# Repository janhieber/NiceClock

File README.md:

# About
This project was started for testing the new KiCad v4
as a replacement for EAGLE.

I want a free ECAD software without the limiations, so
I started this to explore the capabilities of KiCad.

Conclusion: KiCad can be a good replacement for EAGLE and co.  
It has some rough edges, but makes a point with some
great features.

# Nice 3D pics :)

# Current progress
### Hardware

TODO:  
- [ ] schematic
  - [x] LEDs and WS2803 ICs
    - [x] wire up
    - [x] connect to CPU
  - [x] CPU (STM32F1)
  - [ ] real time clock
    - [x] wire up
    - [x] connect to CPU
  - [x] SWD program and serial terminal
- [ ] layout
  - [ ] LEDs
  - [ ] WS2803
  - [ ] STM32 CPU
  - [x] RTC
  - [x] power supply

For the current progress, look at the
[schematic](https://raw.githubusercontent.com/janhieber/NiceClock/master/hardware/doc/schematic.pdf)
and
[layout](https://raw.githubusercontent.com/janhieber/NiceClock/master/hardware/doc/board.pdf) PDFs.

### Software
Software development not started yes.

The software will be written in pure C.  
STM32CubeMX will be used as initialisation code generator.

TODO:  
- [ ] STM32 software
  - [ ] hardware initialisation
  - [ ] cooperative scheduler
  - [ ] real time clock code
  - [ ] LED control code for WS2803 ICs via SPI
  - [ ] DCF77 code
  - [ ] Bootloader for serial program download over UART
- [ ] Software to flash firmware via serial connection

# Community
If you are interessted in this, feel free to contact me.  
I'll also have some spare PCBs when I ordner them, so I'll sell them.

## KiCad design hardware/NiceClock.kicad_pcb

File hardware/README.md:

### Schematic and layout
The schematic and layout was/is created with KiCad version 4.

I'm using some custom symbols, mods and 3D models, they are all
in this folder.

### LED placement
First I placed the LEDs manually. I have drawn a few
circles on the layout and lines from the middle in ~6° steps...

All in all that was really messy and not the way I used to work.  
So I wrote a small Python program to calculate position and angle
of every LED and wite it to the layout file.

Check out the scrit in the *scripts* folder.

### BOM
BOM generation is done using the *bom2csv.xsl* plugin.
Most schemativ parts have a *R* attribute with the reichelt.de
part number.

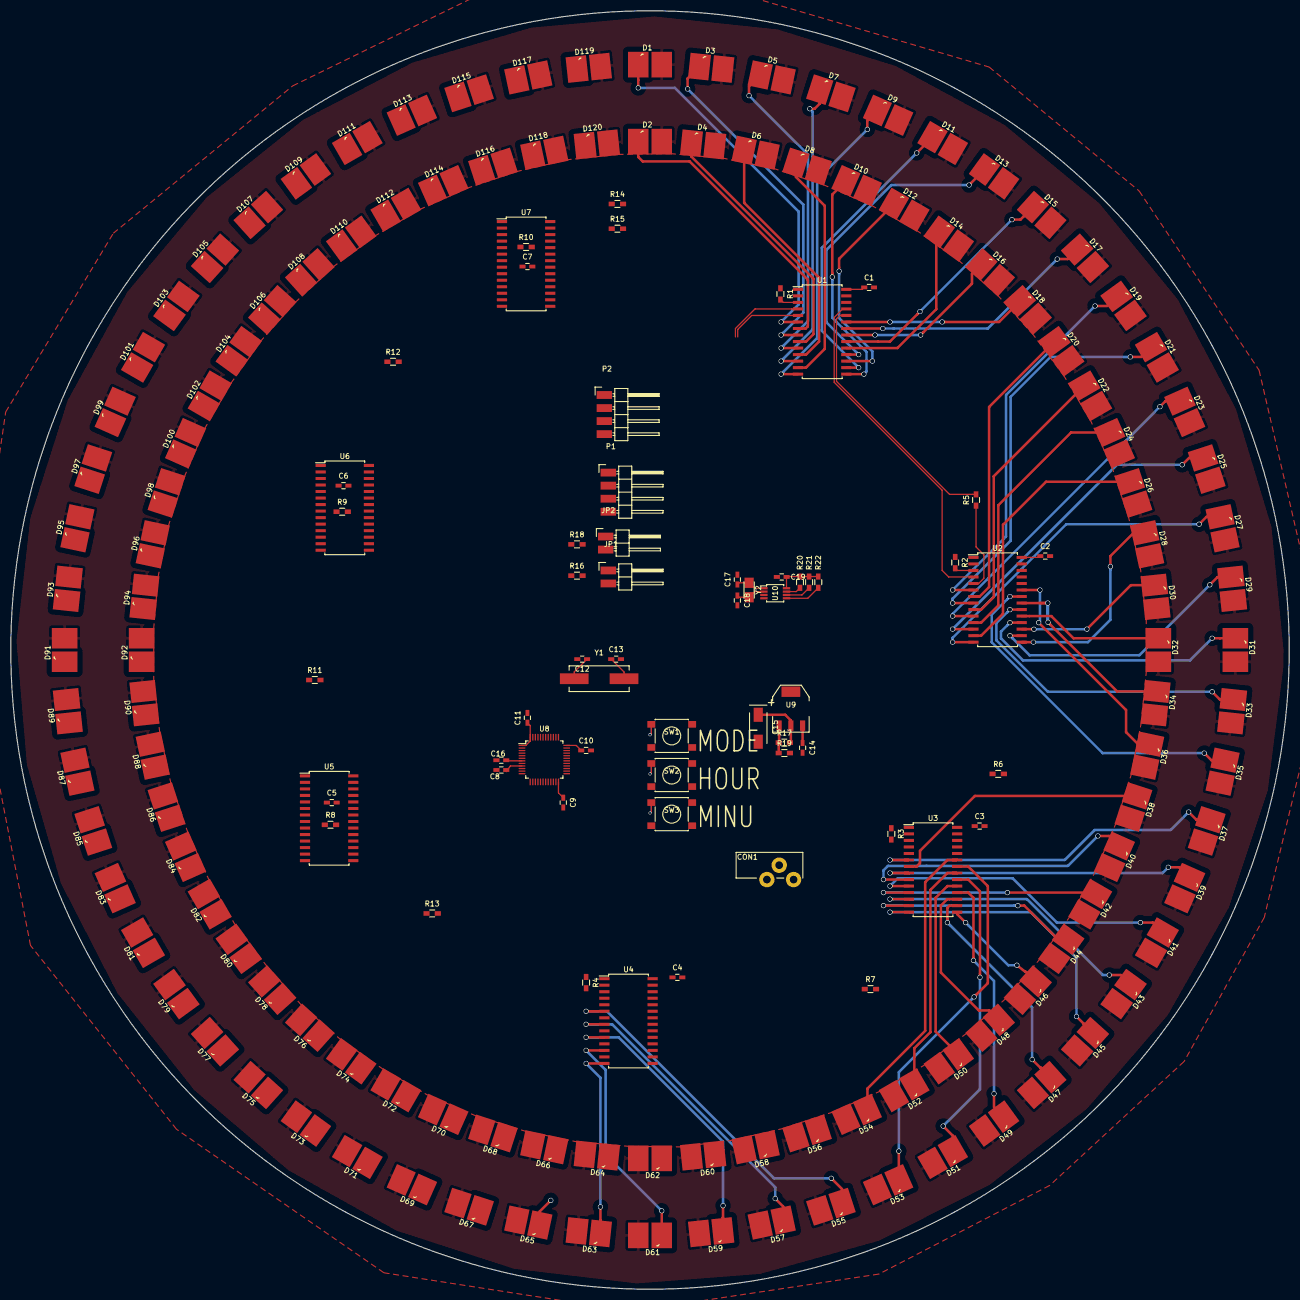
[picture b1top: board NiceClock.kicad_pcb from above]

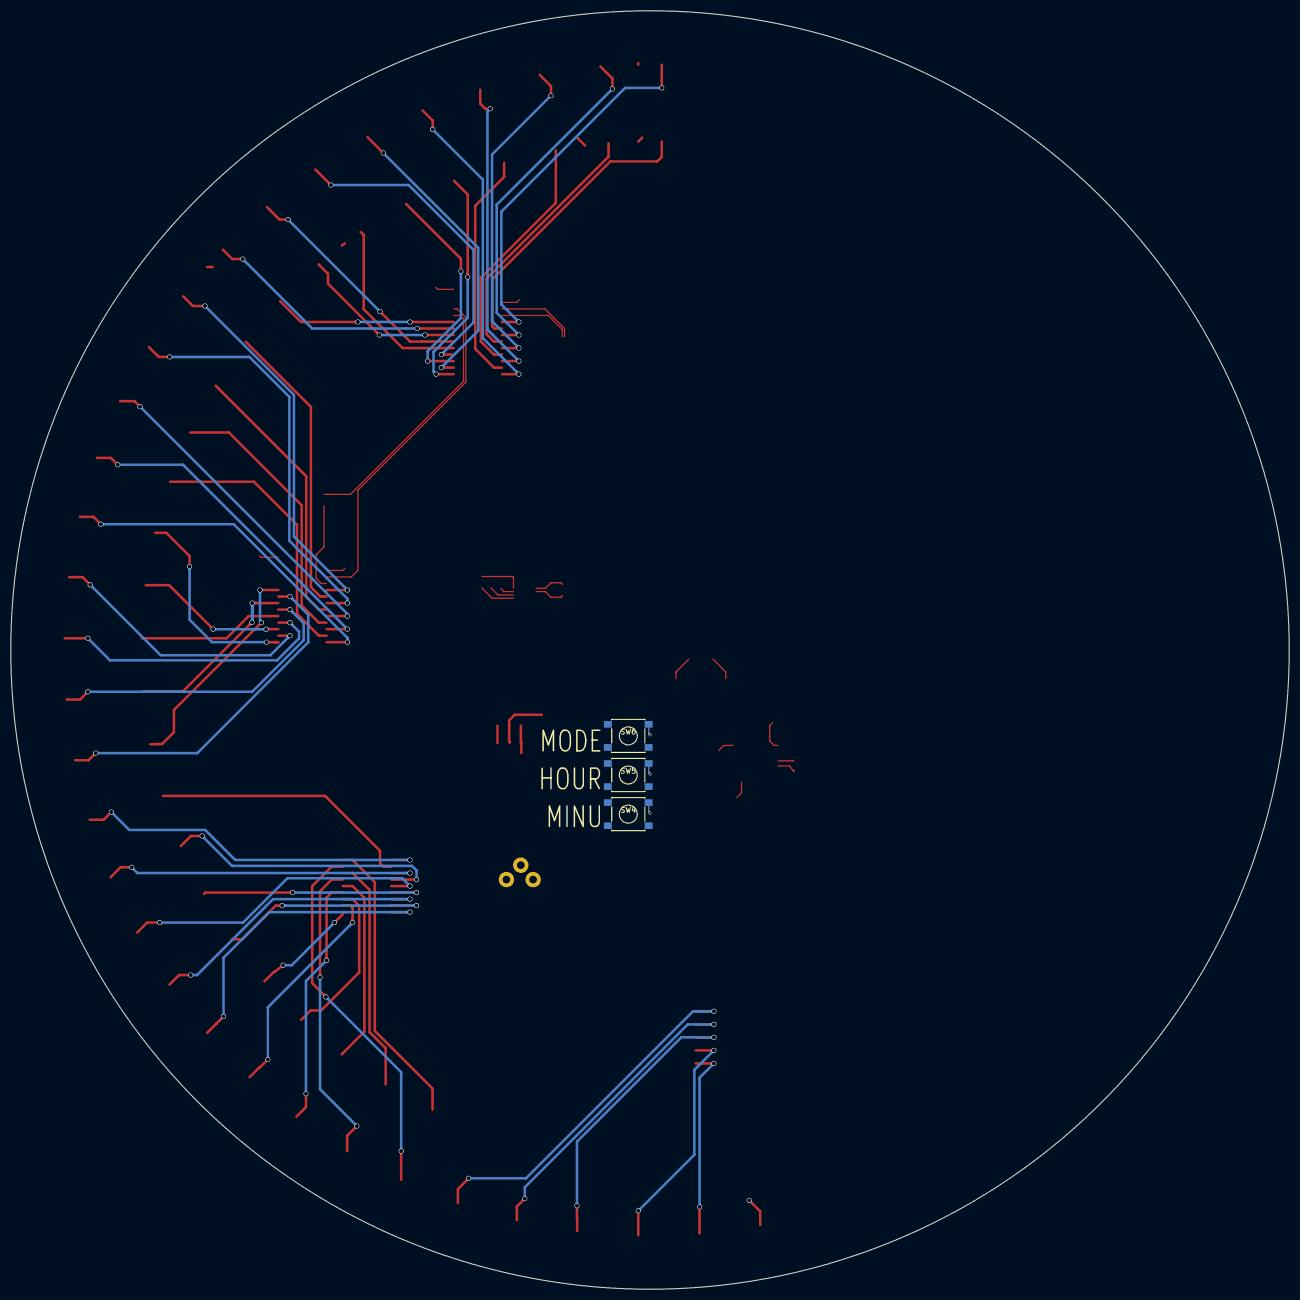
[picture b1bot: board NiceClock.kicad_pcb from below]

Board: 2 copper layers, 249.0 x 249.0 mm, 184 parts (3 on the bottom side), 170 nets.

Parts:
C1, C2, C3, C4, C5, C6, C7, C8, C9, C10, C11, C14, C16, C19: 100n; C_0603_HandSoldering
C12, C13, C17, C18: 22p; C_0603_HandSoldering
C15: 10u; TantalC_SizeC_EIA-6032_Wave
CON1: BARREL_JACK; DC_JACK1
D1, D2, D3, D4, D5, D6, D7, D8, D9, D10, D11, D12, D13, D14, D15, D16, D17, D18, D19, D20, D21, D22, D23, D24, D25, D26, D27, D28, D29, D30, D31, D32, D33, D34, D35, D36, D37, D38, D39, D40, D41, D42, D43, D44, D45, D46, D47, D48, D49, D50, D51, D52, D53, D54, D55, D56, D57, D58, D59, D60, D61, D62, D63, D64, D65, D66, D67, D68, D69, D70, D71, D72, D73, D74, D75, D76, D77, D78, D79, D80, D81, D82, D83, D84, D85, D86, D87, D88, D89, D90, D91, D92, D93, D94, D95, D96, D97, D98, D99, D100, D101, D102, D103, D104, D105, D106, D107, D108, D109, D110, D111, D112, D113, D114, D115, D116, D117, D118, D119, D120: LED; PLCC2
JP1, JP2: Jumper_NO_Small; Pin_Header_SMD_Angled_1x02
P1, P2: CONN_01X04; Pin_Header_SMD_Angled_1x04
R1, R2, R3, R4, R8, R9, R10: 1k; R_0603_HandSoldering
R5, R6, R7, R11, R12, R13: 50R; R_0603_HandSoldering
R14, R15: 200R; R_0603_HandSoldering
R16, R18: 100k; R_0603_HandSoldering
R17: 240R; R_0603_HandSoldering
R19: 400R; R_0603_HandSoldering
R20: 10k; R_0603_HandSoldering
R21, R22: 2k2; R_0603_HandSoldering
SW1, SW2, SW3, SW4, SW5, SW6: SW_PUSH; SW_SPST_PTS645
U1, U2, U3, U4, U5, U6, U7: WS2803; SOIC-28_7.5x17.9mm_Pitch1.27mm
U8: STM32F101C8; LQFP-48_7x7mm_Pitch0.5mm
U9: LM317EMP; SOT-223
U10: MCP7940M; MSOP-8_3x3mm_Pitch0.65mm
Y1: 8MHz; Crystal_HC49-SD_SMD
Y2: 32.768kHz; CRYSTAL_SMD_3.2x1.5

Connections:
+3V3: C1.1, C2.1, C3.1, C4.1, C5.1, C6.1, C7.1, C8.1, C9.1, C10.1, C11.1, C15.1, C19.1, JP1.1, JP2.1, P1.1, P2.1, R17.2, R20.2, R21.2, R22.2, U1.28, U2.28, U3.28, U4.28, U5.28, U6.28, U7.28, U8.1, U8.9, U8.24, U8.36, U8.48, U9.2, U10.8
+5V: C14.1, CON1.1, D1.2, D2.2, D3.2, D4.2, D5.2, D6.2, D7.2, D8.2, D9.2, D10.2, D11.2, D12.2, D13.2, D14.2, D15.2, D16.2, D17.2, D18.2, D19.2, D20.2, D21.2, D22.2, D23.2, D24.2, D25.2, D26.2, D27.2, D28.2, D29.2, D30.2, D31.2, D32.2, D33.2, D34.2, D35.2, D36.2, D37.2, D38.2, D39.2, D40.2, D41.2, D42.2, D43.2, D44.2, D45.2, D46.2, D47.2, D48.2, D49.2, D50.2, D51.2, D52.2, D53.2, D54.2, D55.2, D56.2, D57.2, D58.2, D59.2, D60.2, D61.2, D62.2, D63.2, D64.2, D65.2, D66.2, D67.2, D68.2, D69.2, D70.2, D71.2, D72.2, D73.2, D74.2, D75.2, D76.2, D77.2, D78.2, D79.2, D80.2, D81.2, D82.2, D83.2, D84.2, D85.2, D86.2, D87.2, D88.2, D89.2, D90.2, D91.2, D92.2, D93.2, D94.2, D95.2, D96.2, D97.2, D98.2, D99.2, D100.2, D101.2, D102.2, D103.2, D104.2, D105.2, D106.2, D107.2, D108.2, D109.2, D110.2, D111.2, D112.2, D113.2, D114.2, D115.2, D116.2, D117.2, D118.2, D119.2, D120.2, U9.3
/BOOT0: JP1.2, R16.1, U8.44
/BOOT1: JP2.2, R18.1, U8.20
/LED_CLOCK: U1.4, U8.15
/LED_DATA: U1.5, U8.17
/OSC_IN: C12.1, U8.5, Y1.1
/OSC_OUT: C13.1, U8.6, Y1.2
/RTC_MFP: R20.1, U8.41, U10.7
/RTC_SCL: R21.1, U8.42, U10.6
/RTC_SDA: R22.1, U8.43, U10.5
/SWCLK: P1.3, U8.37
/SWDIO: P1.2, U8.34
/SW_H: SW2.1, SW5.1, U8.27
/SW_M: SW3.1, SW4.1, U8.26
/SW_MODE: SW1.1, SW6.1, U8.28
/USART1_RX: P2.3, U8.31
/USART1_TX: P2.2, U8.30
GND: C1.2, C2.2, C3.2, C4.2, C5.2, C6.2, C7.2, C8.2, C9.2, C10.2, C11.2, C12.2, C13.2, C14.2, C15.2, C16.2, C17.2, C18.2, C19.2, CON1.2, CON1.3, P1.4, P2.4, R1.1, R2.1, R3.1, R4.1, R8.1, R9.1, R10.1, R14.1, R15.1, R16.2, R18.2, R19.2, SW1.2, SW2.2, SW3.2, SW4.2, SW5.2, SW6.2, U1.1, U2.1, U3.1, U4.1, U5.1, U6.1, U7.1, U8.8, U8.23, U8.35, U8.47, U10.4
unnamed: C16.1, U8.7
unnamed: C17.1, U10.1, Y2.1
unnamed: C18.1, U10.2, Y2.2
unnamed: D1.1, U1.6
unnamed: D2.1, U1.7
unnamed: D3.1, U1.8
unnamed: D4.1, U1.9
unnamed: D5.1, U1.10
unnamed: D6.1, U1.11
unnamed: D7.1, U1.12
unnamed: D8.1, U1.13
unnamed: D9.1, U1.14
unnamed: D10.1, U1.15
unnamed: D11.1, U1.16
unnamed: D12.1, U1.17
unnamed: D13.1, U1.18
unnamed: D14.1, U1.19
unnamed: D15.1, U1.20
unnamed: D16.1, U1.21
unnamed: D17.1, U1.22
unnamed: D18.1, U1.23
unnamed: D19.1, U2.6
unnamed: D20.1, U2.7
unnamed: D21.1, U2.8
unnamed: D22.1, U2.9
unnamed: D23.1, U2.10
unnamed: D24.1, U2.11
unnamed: D25.1, U2.12
unnamed: D26.1, U2.13
unnamed: D27.1, U2.14
unnamed: D28.1, U2.15
unnamed: D29.1, U2.16
unnamed: D30.1, U2.17
unnamed: D31.1, U2.18
unnamed: D32.1, U2.19
unnamed: D33.1, U2.20
unnamed: D34.1, U2.21
unnamed: D35.1, U2.22
unnamed: D36.1, U2.23
unnamed: D37.1, U3.6
unnamed: D38.1, U3.7
unnamed: D39.1, U3.8
unnamed: D40.1, U3.9
unnamed: D41.1, U3.10
unnamed: D42.1, U3.11
unnamed: D43.1, U3.12
unnamed: D44.1, U3.13
unnamed: D45.1, U3.14
unnamed: D46.1, U3.15
unnamed: D47.1, U3.16
unnamed: D48.1, U3.17
unnamed: D49.1, U3.18
unnamed: D50.1, U3.19
unnamed: D51.1, U3.20
unnamed: D52.1, U3.21
unnamed: D53.1, U3.22
unnamed: D54.1, U3.23
unnamed: D55.1, U4.6
unnamed: D56.1, U4.7
unnamed: D57.1, U4.8
unnamed: D58.1, U4.9
unnamed: D59.1, U4.10
unnamed: D60.1, U4.11
unnamed: D61.1, U4.12
unnamed: D62.1, U4.13
unnamed: D63.1, U4.14
unnamed: D64.1, U4.15
unnamed: D65.1, U4.16
unnamed: D66.1, U4.17
unnamed: D67.1, U4.18
unnamed: D68.1, U4.19
unnamed: D69.1, U4.20
unnamed: D70.1, U4.21
unnamed: D71.1, U4.22
unnamed: D72.1, U4.23
unnamed: D73.1, U5.6
unnamed: D74.1, U5.7
unnamed: D75.1, U5.8
unnamed: D76.1, U5.9
unnamed: D77.1, U5.10
unnamed: D78.1, U5.11
unnamed: D79.1, U5.12
unnamed: D80.1, U5.13
unnamed: D81.1, U5.14
unnamed: D82.1, U5.15
unnamed: D83.1, U5.16
unnamed: D84.1, U5.17
unnamed: D85.1, U5.18
unnamed: D86.1, U5.19
unnamed: D87.1, U5.20
unnamed: D88.1, U5.21
unnamed: D89.1, U5.22
unnamed: D90.1, U5.23
unnamed: D91.1, U6.6
unnamed: D92.1, U6.7
unnamed: D93.1, U6.8
unnamed: D94.1, U6.9
unnamed: D95.1, U6.10
unnamed: D96.1, U6.11
unnamed: D97.1, U6.12
unnamed: D98.1, U6.13
unnamed: D99.1, U6.14
unnamed: D100.1, U6.15
unnamed: D101.1, U6.16
unnamed: D102.1, U6.17
unnamed: D103.1, U6.18
unnamed: D104.1, U6.19
unnamed: D105.1, U6.20
unnamed: D106.1, U6.21
unnamed: D107.1, U6.22
unnamed: D108.1, U6.23
unnamed: D109.1, U7.6
unnamed: D110.1, U7.7
unnamed: D111.1, U7.8
unnamed: D112.1, U7.9
unnamed: D113.1, U7.10
unnamed: D114.1, U7.11
unnamed: D115.1, U7.12
unnamed: D116.1, U7.13
unnamed: D117.1, U7.14
unnamed: D118.1, U7.15
unnamed: D119.1, U7.16
unnamed: D120.1, U7.17
unnamed: R1.2, U1.3
unnamed: R2.2, U2.3
unnamed: R3.2, U3.3
unnamed: R4.2, U4.3
unnamed: R5.1, U2.5
unnamed: R5.2, U1.24
unnamed: R6.1, U3.5
unnamed: R6.2, U2.24
unnamed: R7.1, U4.5
unnamed: R7.2, U3.24
unnamed: R8.2, U5.3
unnamed: R9.2, U6.3
unnamed: R10.2, U7.3
unnamed: R11.1, U6.5
unnamed: R11.2, U5.24
unnamed: R12.1, U7.5
unnamed: R12.2, U6.24
unnamed: R13.1, U5.5
unnamed: R13.2, U4.24
unnamed: R14.2, U7.24
unnamed: R15.2, U7.25
unnamed: R17.1, R19.1, U9.1
unnamed: U1.25, U2.4
unnamed: U2.25, U3.4
unnamed: U3.25, U4.4
unnamed: U4.25, U5.4
unnamed: U5.25, U6.4
unnamed: U6.25, U7.4

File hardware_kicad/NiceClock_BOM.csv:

Reference, Value, Footprint, Datasheet, R
D2,LED,custom_janh:PLCC2,
D3,LED,custom_janh:PLCC2,
U8,STM32F101C8,Housings_QFP:LQFP-48_7x7mm_Pitch0.5mm,
D1,LED,custom_janh:PLCC2,
C9,100n,Capacitors_SMD:C_0603_HandSoldering,
Y1,8MHz,Crystals:Crystal_HC49-SD_SMD,http://cdn-reichelt.de/documents/datenblatt/B400/DS_HC-49US-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,8,0000-HC49-SMD
C12,22p,Capacitors_SMD:C_0603_HandSoldering,
C13,22p,Capacitors_SMD:C_0603_HandSoldering,
U9,LM317EMP,TO_SOT_Packages_SMD:SOT-223,http://cdn-reichelt.de/documents/datenblatt/A200/DS_LM_317.pdf,LM 317 EMP
R17,240R,Resistors_SMD:R_0603_HandSoldering,
R19,400R,Resistors_SMD:R_0603_HandSoldering,
C15,10u,Capacitors_Tantalum_SMD:TantalC_SizeC_EIA-6032_Wave,http://cdn-reichelt.de/documents/datenblatt/B300/SMDTAN_xx.pdf,SMD TAN.10/16
C8,100n,Capacitors_SMD:C_0603_HandSoldering,
C10,100n,Capacitors_SMD:C_0603_HandSoldering,
C16,100n,Capacitors_SMD:C_0603_HandSoldering,
C14,100n,Capacitors_SMD:C_0603_HandSoldering,
R20,240R,Resistors_SMD:R_0603_HandSoldering,
R16,100k,Resistors_SMD:R_0603_HandSoldering,
C11,100n,Capacitors_SMD:C_0603_HandSoldering,
P1,CONN_01X04,custom_janh:Pin_Header_SMD_Angled_1x04,
U1,WS2803,Housings_SOIC:SOIC-28_7.5x17.9mm_Pitch1.27mm,
D4,LED,custom_janh:PLCC2,
D6,LED,custom_janh:PLCC2,
D7,LED,custom_janh:PLCC2,
D5,LED,custom_janh:PLCC2,
D8,LED,custom_janh:PLCC2,
D10,LED,custom_janh:PLCC2,
D11,LED,custom_janh:PLCC2,
D9,LED,custom_janh:PLCC2,
D12,LED,custom_janh:PLCC2,
D14,LED,custom_janh:PLCC2,
D15,LED,custom_janh:PLCC2,
D13,LED,custom_janh:PLCC2,
D16,LED,custom_janh:PLCC2,
D17,LED,custom_janh:PLCC2,
D18,LED,custom_janh:PLCC2,
D20,LED,custom_janh:PLCC2,
D21,LED,custom_janh:PLCC2,
D19,LED,custom_janh:PLCC2,
U2,WS2803,Housings_SOIC:SOIC-28_7.5x17.9mm_Pitch1.27mm,
D22,LED,custom_janh:PLCC2,
D24,LED,custom_janh:PLCC2,
D25,LED,custom_janh:PLCC2,
D23,LED,custom_janh:PLCC2,
D26,LED,custom_janh:PLCC2,
D28,LED,custom_janh:PLCC2,
D29,LED,custom_janh:PLCC2,
D27,LED,custom_janh:PLCC2,
D30,LED,custom_janh:PLCC2,
D32,LED,custom_janh:PLCC2,
D33,LED,custom_janh:PLCC2,
D31,LED,custom_janh:PLCC2,
D34,LED,custom_janh:PLCC2,
D35,LED,custom_janh:PLCC2,
D36,LED,custom_janh:PLCC2,
D38,LED,custom_janh:PLCC2,
D39,LED,custom_janh:PLCC2,
D37,LED,custom_janh:PLCC2,
U3,WS2803,Housings_SOIC:SOIC-28_7.5x17.9mm_Pitch1.27mm,
D40,LED,custom_janh:PLCC2,
D42,LED,custom_janh:PLCC2,
D43,LED,custom_janh:PLCC2,
D41,LED,custom_janh:PLCC2,
D44,LED,custom_janh:PLCC2,
D46,LED,custom_janh:PLCC2,
D47,LED,custom_janh:PLCC2,
D45,LED,custom_janh:PLCC2,
D48,LED,custom_janh:PLCC2,
D50,LED,custom_janh:PLCC2,
D51,LED,custom_janh:PLCC2,
D49,LED,custom_janh:PLCC2,
D52,LED,custom_janh:PLCC2,
D53,LED,custom_janh:PLCC2,
D54,LED,custom_janh:PLCC2,
D56,LED,custom_janh:PLCC2,
D57,LED,custom_janh:PLCC2,
D55,LED,custom_janh:PLCC2,
U4,WS2803,Housings_SOIC:SOIC-28_7.5x17.9mm_Pitch1.27mm,
D58,LED,custom_janh:PLCC2,
D60,LED,custom_janh:PLCC2,
D61,LED,custom_janh:PLCC2,
D59,LED,custom_janh:PLCC2,
D62,LED,custom_janh:PLCC2,
D64,LED,custom_janh:PLCC2,
D65,LED,custom_janh:PLCC2,
D63,LED,custom_janh:PLCC2,
D66,LED,custom_janh:PLCC2,
D68,LED,custom_janh:PLCC2,
D69,LED,custom_janh:PLCC2,
D67,LED,custom_janh:PLCC2,
D70,LED,custom_janh:PLCC2,
D71,LED,custom_janh:PLCC2,
D72,LED,custom_janh:PLCC2,
D74,LED,custom_janh:PLCC2,
D75,LED,custom_janh:PLCC2,
D73,LED,custom_janh:PLCC2,
U5,WS2803,Housings_SOIC:SOIC-28_7.5x17.9mm_Pitch1.27mm,
D76,LED,custom_janh:PLCC2,
D78,LED,custom_janh:PLCC2,
D79,LED,custom_janh:PLCC2,
D77,LED,custom_janh:PLCC2,
D80,LED,custom_janh:PLCC2,
D82,LED,custom_janh:PLCC2,
D83,LED,custom_janh:PLCC2,
D81,LED,custom_janh:PLCC2,
D84,LED,custom_janh:PLCC2,
D86,LED,custom_janh:PLCC2,
D87,LED,custom_janh:PLCC2,
D85,LED,custom_janh:PLCC2,
D88,LED,custom_janh:PLCC2,
D89,LED,custom_janh:PLCC2,
D90,LED,custom_janh:PLCC2,
D92,LED,custom_janh:PLCC2,
D93,LED,custom_janh:PLCC2,
D91,LED,custom_janh:PLCC2,
U6,WS2803,Housings_SOIC:SOIC-28_7.5x17.9mm_Pitch1.27mm,
D94,LED,custom_janh:PLCC2,
D96,LED,custom_janh:PLCC2,
D97,LED,custom_janh:PLCC2,
D95,LED,custom_janh:PLCC2,
D98,LED,custom_janh:PLCC2,
D100,LED,custom_janh:PLCC2,
D101,LED,custom_janh:PLCC2,
D99,LED,custom_janh:PLCC2,
D102,LED,custom_janh:PLCC2,
D104,LED,custom_janh:PLCC2,
D105,LED,custom_janh:PLCC2,
D103,LED,custom_janh:PLCC2,
D106,LED,custom_janh:PLCC2,
D107,LED,custom_janh:PLCC2,
D108,LED,custom_janh:PLCC2,
R1,1k,Resistors_SMD:R_0603_HandSoldering,
R5,50R,Resistors_SMD:R_0603_HandSoldering,
JP1,Jumper_NO_Small,custom_janh:Pin_Header_SMD_Angled_1x02,
JP2,Jumper_NO_Small,custom_janh:Pin_Header_SMD_Angled_1x02,
R18,100k,Resistors_SMD:R_0603_HandSoldering,
R6,50R,Resistors_SMD:R_0603_HandSoldering,
R2,1k,Resistors_SMD:R_0603_HandSoldering,
R3,1k,Resistors_SMD:R_0603_HandSoldering,
R7,50R,Resistors_SMD:R_0603_HandSoldering,
R4,1k,Resistors_SMD:R_0603_HandSoldering,
R13,50R,Resistors_SMD:R_0603_HandSoldering,
R8,1k,Resistors_SMD:R_0603_HandSoldering,
R9,1k,Resistors_SMD:R_0603_HandSoldering,
R11,50R,Resistors_SMD:R_0603_HandSoldering,
C2,100n,Capacitors_SMD:C_0603_HandSoldering,
C1,100n,Capacitors_SMD:C_0603_HandSoldering,
C3,100n,Capacitors_SMD:C_0603_HandSoldering,
C4,100n,Capacitors_SMD:C_0603_HandSoldering,
C5,100n,Capacitors_SMD:C_0603_HandSoldering,
C6,100n,Capacitors_SMD:C_0603_HandSoldering,
D110,LED,custom_janh:PLCC2,
D111,LED,custom_janh:PLCC2,
D109,LED,custom_janh:PLCC2,
U7,WS2803,Housings_SOIC:SOIC-28_7.5x17.9mm_Pitch1.27mm,
D112,LED,custom_janh:PLCC2,
D114,LED,custom_janh:PLCC2,
D115,LED,custom_janh:PLCC2,
D113,LED,custom_janh:PLCC2,
D116,LED,custom_janh:PLCC2,
D118,LED,custom_janh:PLCC2,
D119,LED,custom_janh:PLCC2,
D117,LED,custom_janh:PLCC2,
D120,LED,custom_janh:PLCC2,
R10,1k,Resistors_SMD:R_0603_HandSoldering,
R12,50R,Resistors_SMD:R_0603_HandSoldering,
R15,200R,Resistors_SMD:R_0603_HandSoldering,
R14,200R,Resistors_SMD:R_0603_HandSoldering,
C7,100n,Capacitors_SMD:C_0603_HandSoldering,

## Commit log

2015-12-07 initial design stuff
2015-12-07 kicad changes + new eagle schematic
2015-12-18 kicad updates
2015-12-25 reworked schematic + new board
2015-12-25 placed LEDs and other stuff
2015-12-26 some tracks and 3D drawing
2015-12-27 pcb updates
2015-12-27 update docu stuff
2015-12-27 use relative path to 3D models
2015-12-28 added switches, DC jack + some routing
2015-12-30 some updates
